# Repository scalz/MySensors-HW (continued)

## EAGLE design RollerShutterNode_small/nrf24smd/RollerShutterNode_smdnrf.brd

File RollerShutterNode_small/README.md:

# RollerShutterNode SMD version

It is a board for controlling rollershutter (0-100%) and detecting end stops.. Two relays for motor (UP and DOWN) and ACS712 for current sense of motor. 
You can connect 3 push buttons or an external i2c tactile device. This board can be used as dual relay board too, with current sense. It can control 12-220V motors.

Note : it is still in dev.

- Atmel328p TQFP
- NRF24 smd footprint
- ATSHA204A authentication footprint
- eeprom footprint for OTA
- ACS712 footprint
- 2x 5Amp relays : OMRON G6D-1A-ASI protected by TVS diode & small capacitor
- ac dc stepdown 220V-5V : HILINK_HLK-PM01 protected by varistor & ptc fuse
- 5mm pitch screw terminals
- I2C connector for optional tactile sensor chip
- 47mm x 48mm

Arduino Pin description :
- A0 : ADC ACS712
- A3 : ATSHA204A data
- D6 : Down Relay
- D7 : Up relay
- I2C connector : SDA, SCL, D3, D4

DC connectors : 
- SPI for programming Atmel328p
- FTDI for bootloading
- A1 : Up button
- A2 : Down button
- D5 : Stop button

AC Connector description :
- N : Neutral (Neutre)
- L : Live (Phase)
- 12_220 : optional. If using 220v motor, you need to tie it with Source on Motor Connector

Motor Connector description :
- Up : Up relay for motor
- Down : Down relay for motor
- Source : 12-24v motor source. If using 220v motor, tie it with 12_220 on AC Connector

In progress : 
- sketch for rollershutter (buttons, calibration functions, controlling 0-100%). 
- add Bill of Materials
- add gerbers for Seeed, Itead, and OSH fabhouses.

OPEN SOURCE

Copyright Scalz (2015). [Attribution-ShareAlike CC BY-SA](https://creativecommons.org/licenses/)

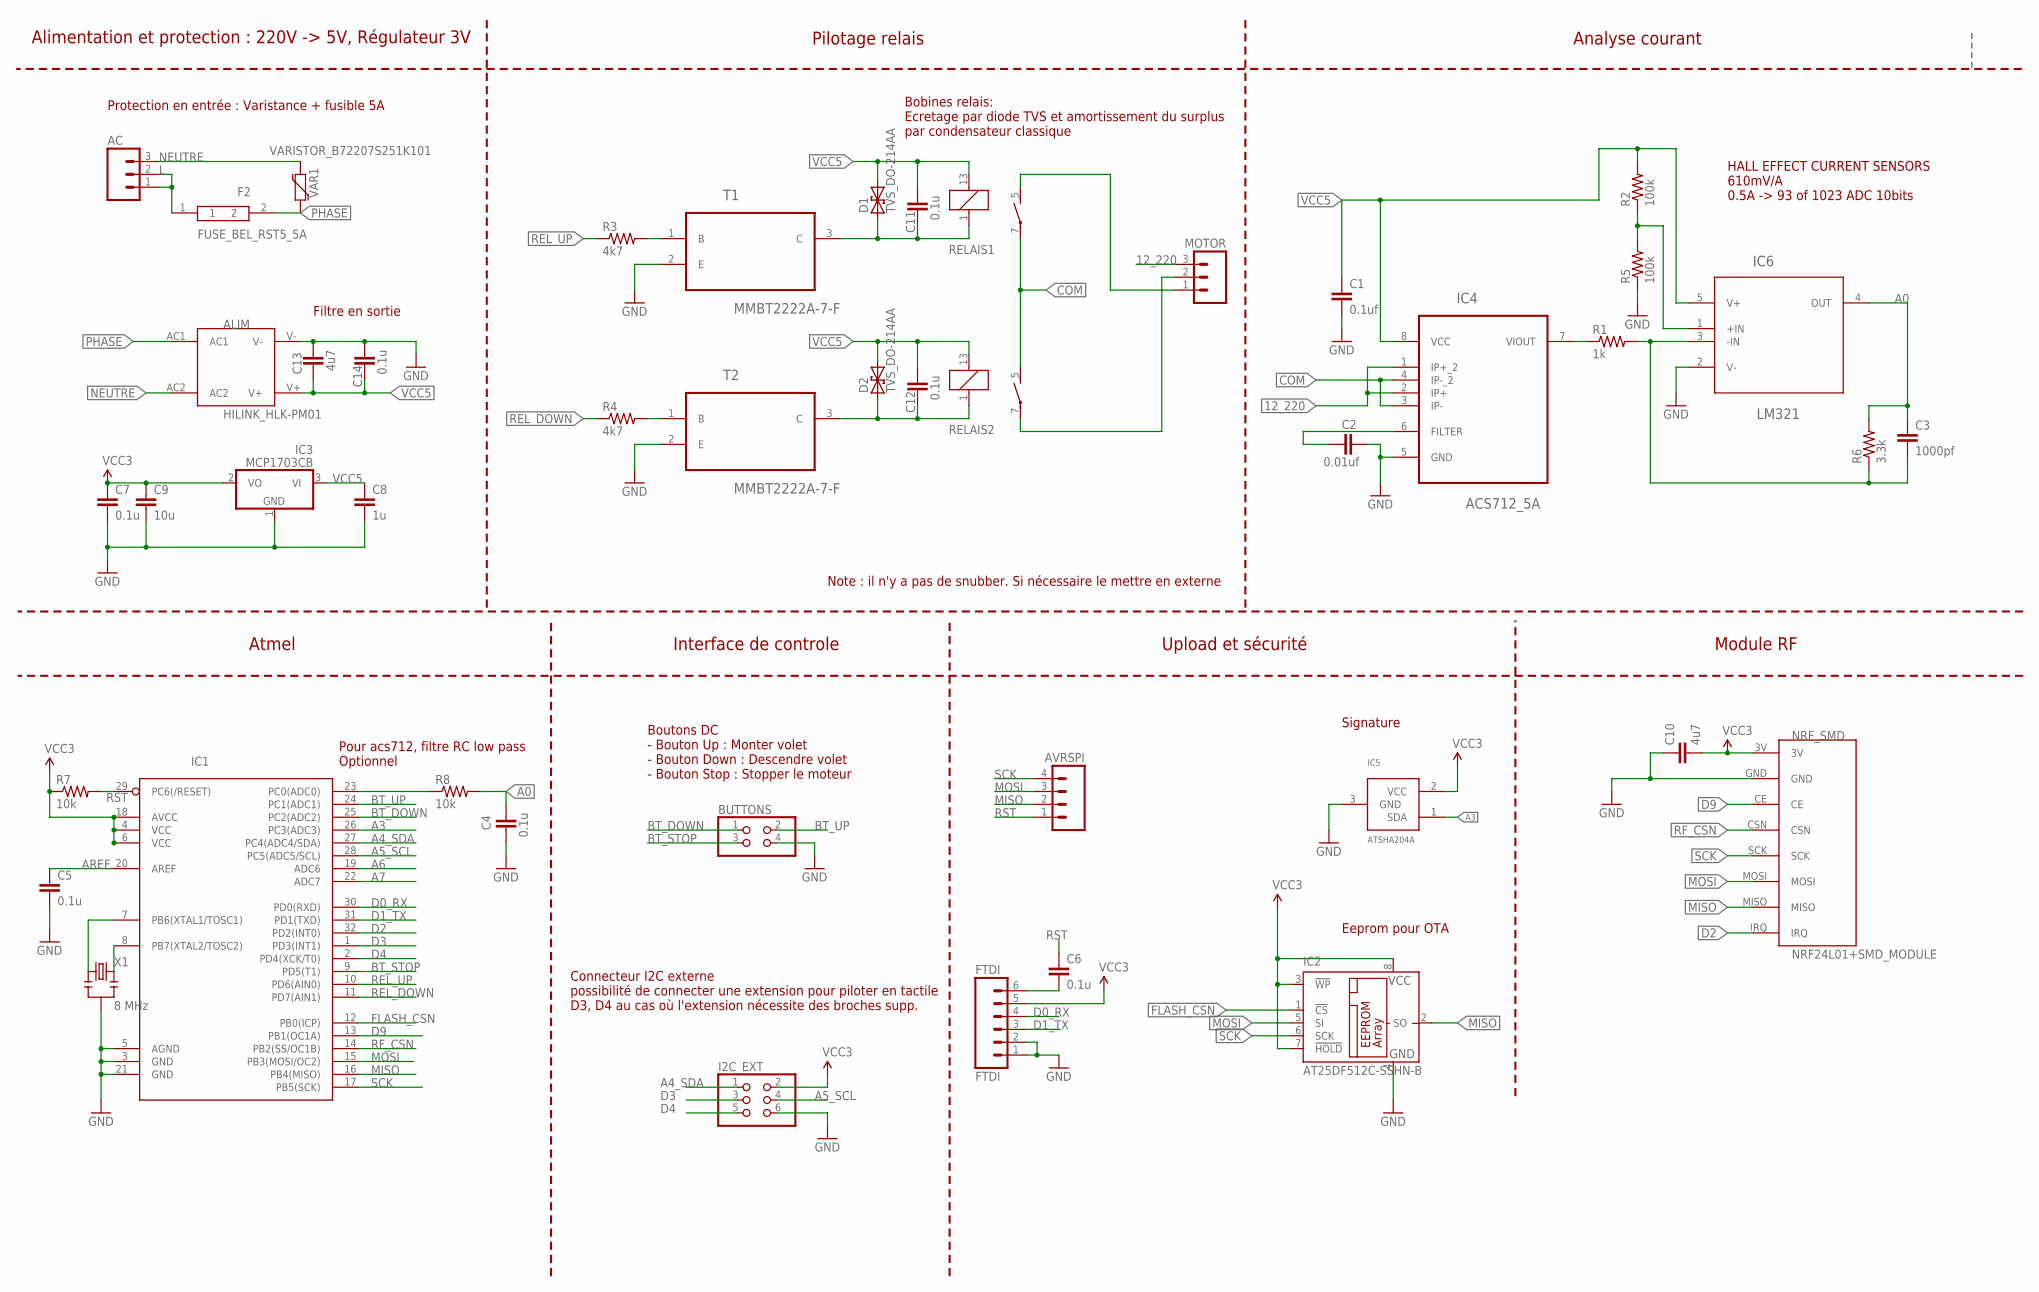
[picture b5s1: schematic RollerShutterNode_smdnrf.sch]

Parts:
AC: M03-SCREW-5MM; SCREWTERMINAL-5MM-3
ALIM: HILINK_HLK-PM01
AVRSPI: M04PTH; 1X04
BUTTONS: PINHD-2X2; 2X02
C1: 0.1uf; 0805-CAP
C2: 0.01uf; 0805-CAP
C3: 1000pf; 0805-CAP
C4, C5, C6, C7, C11, C12, C14: 0.1u; 0805-CAP
C8: 1u; 0805-CAP
C9: 10u; 0805-CAP
C10, C13: 4u7; 0805-CAP
D1, D2: TVS_DO-214AA
F2: FUSE_BEL_RST5_5A
FTDI: FTDI; 1X06
I2C_EXT: PINHD-2X3; 2X03
IC1: ATMega-328; TQFP32-08
IC2: AT25DF512C-SSHN-B; SO-08
IC3: MCP1703CB; SOT23
IC4: ACS712_5A; SOIC127P600X175-8N
IC5: ATSHA204A; SOT23
IC6: LM321; SOT95P285X120-5N
MOTOR: M03-SCREW-5MM; SCREWTERMINAL-5MM-3
NRF_SMD: NRF24L01+SMD_MODULE
R1: 1k; 0805-RES
R2, R5: 100k; 0805-RES
R3, R4: 4k7; 0805-RES
R6: 3.3k; 0805-RES
R7, R8: 10k; 0805-RES
RELAIS1, RELAIS2: Relais G6D; G6D
T1, T2: MMBT2222A-7-F; SOT103P240X110-3N
VAR1: VARISTOR_B72207S251K101
X1: 8 MHz; RESONATOR-SMD

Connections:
12_220: IC4.1 (IP+_2), IC4.2 (IP+), MOTOR.3
A0: C3.1, C4.2, IC6.4 (OUT), R6.2, R8.2
A3: IC1.26 (PC3(ADC3)), IC5.1 (SDA)
A4_SDA: I2C_EXT.1, IC1.27 (PC4(ADC4/SDA))
A5_SCL: I2C_EXT.4, IC1.28 (PC5(ADC5/SCL))
A6: IC1.19 (ADC6)
A7: IC1.22 (ADC7)
AREF: C5.1, IC1.20 (AREF)
BT_DOWN: BUTTONS.1, IC1.25 (PC2(ADC2))
BT_STOP: BUTTONS.3, IC1.9 (PD5(T1))
BT_UP: BUTTONS.2, IC1.24 (PC1(ADC1))
COM: IC4.3 (IP-), IC4.4 (IP-_2), RELAIS1.7, RELAIS2.5 (S)
D0_RX: FTDI.4, IC1.30 (PD0(RXD))
D1_TX: FTDI.3, IC1.31 (PD1(TXD))
D2: IC1.32 (PD2(INT0)), NRF_SMD.IRQ
D3: I2C_EXT.3, IC1.1 (PD3(INT1))
D4: I2C_EXT.5, IC1.2 (PD4(XCK/T0))
D9: IC1.13 (PB1(OC1A)), NRF_SMD.CE
FLASH_CSN: IC1.12 (PB0(ICP)), IC2.1 (!CS)
GND: ALIM.V-, BUTTONS.4, C1.2, C2.2, C4.1, C5.2, C7.2, C8.2, C9.2, C10.1, C13.2, C14.2, FTDI.1, FTDI.2, I2C_EXT.6, IC1.3 (GND), IC1.5 (AGND), IC1.21 (GND), IC2.4 (GND), IC3.1 (GND), IC4.5 (GND), IC5.3 (GND), IC6.2 (V-), NRF_SMD.GND, R5.1, T1.2 (E), T2.2 (E), X1.2
L: AC.1, AC.2, F2.1
MISO: AVRSPI.2, IC1.16 (PB4(MISO)), IC2.2 (SO), NRF_SMD.MISO
MOSI: AVRSPI.3, IC1.15 (PB3(MOSI/OC2)), IC2.5 (SI), NRF_SMD.MOSI
unnamed: C2.1, IC4.6 (FILTER)
unnamed: IC4.7 (VIOUT), R1.1
unnamed: R3.2, T1.1 (B)
unnamed: R4.2, T2.1 (B)
unnamed: C12.1, D2.A (1), RELAIS2.1, T2.3 (C)
unnamed: MOTOR.1, RELAIS1.5 (S)
unnamed: C11.1, D1.A (1), RELAIS1.1, T1.3 (C)
unnamed: MOTOR.2, RELAIS2.7
unnamed: C3.2, IC6.3 (-IN), R1.2, R6.1
unnamed: IC6.1 (+IN), R2.1, R5.2
unnamed: IC1.7 (PB6(XTAL1/TOSC1)), X1.1
unnamed: IC1.23 (PC0(ADC0)), R8.1
unnamed: C6.2, FTDI.6
unnamed: IC1.8 (PB7(XTAL2/TOSC2)), X1.3
NEUTRE: AC.3, ALIM.AC2, VAR1.1
PHASE: ALIM.AC1, F2.2, VAR1.2
REL_DOWN: IC1.11 (PD7(AIN1)), R4.1
REL_UP: IC1.10 (PD6(AIN0)), R3.1
RF_CSN: IC1.14 (PB2(SS/OC1B)), NRF_SMD.CSN
RST: AVRSPI.1, C6.1, IC1.29 (PC6(/RESET)), R7.2
SCK: AVRSPI.4, IC1.17 (PB5(SCK)), IC2.6 (SCK), NRF_SMD.SCK
VCC: C7.1, C9.1, C10.2, FTDI.5, I2C_EXT.2, IC1.4 (VCC), IC1.6 (VCC), IC1.18 (AVCC), IC2.3 (!WP), IC2.7 (!HOLD), IC2.8 (VCC), IC3.2 (VO), IC5.2 (VCC), NRF_SMD.3V, R7.1
VCC5: ALIM.V+, C1.1, C8.1, C11.2, C12.2, C13.1, C14.1, D1.C (2), D2.C (2), IC3.3 (VI), IC4.8 (VCC), IC6.5 (V+), R2.2, RELAIS1.13 (2), RELAIS2.13 (2)

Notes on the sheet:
HALL EFFECT CURRENT SENSORS 610mV/A 0.5A -> 93 of 1023 ADC 10bits
Eeprom pour OTA
Signature
Interface de controle
Boutons DC - Bouton Up : Monter volet - Bouton Down : Descendre volet - Bouton Stop : Stopper le moteur
Connecteur I2C externe possibilité de connecter une extension pour piloter en tactile D3, D4 au cas où l'extension nécessite des broches supp.
Protection en entrée : Varistance + fusible 5A
Bobines relais: Ecretage par diode TVS et amortissement du surplus par condensateur classique
Alimentation et protection : 220V -> 5V, Régulateur 3V
Pilotage relais
Analyse courant
Upload et sécurité
Module RF
Atmel
Pour acs712, filtre RC low pass Optionnel
Filtre en sortie
Note : il n'y a pas de snubber. Si nécessaire le mettre en externe

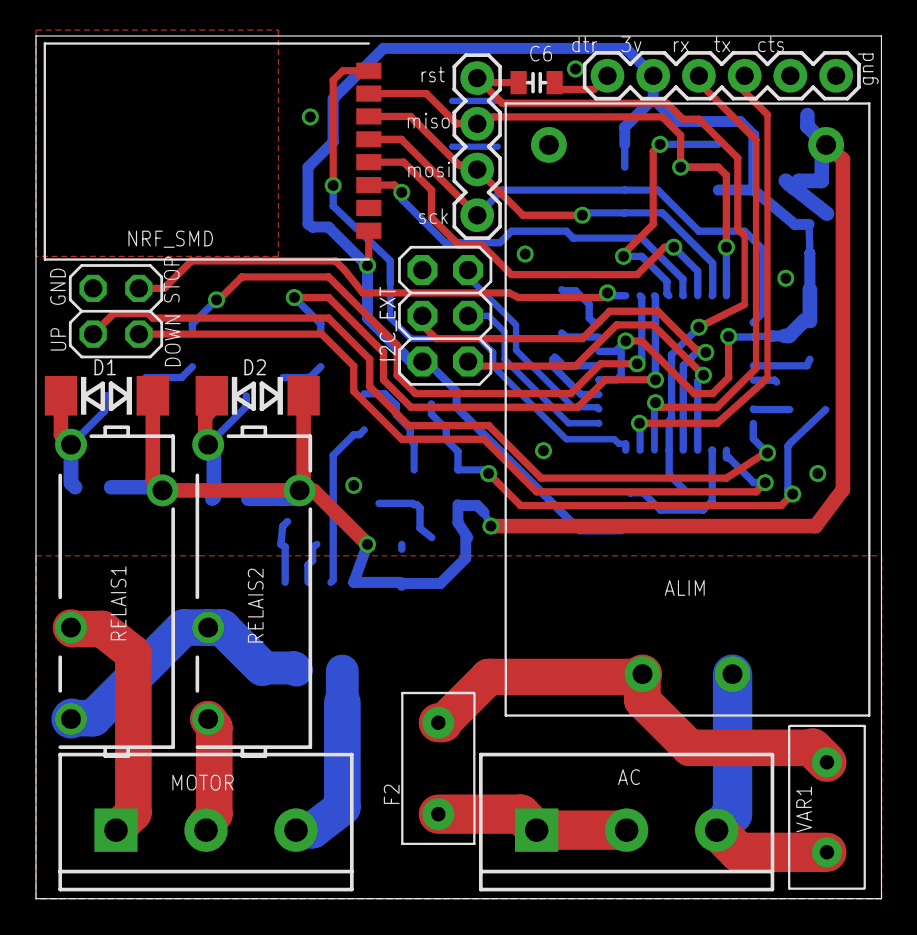
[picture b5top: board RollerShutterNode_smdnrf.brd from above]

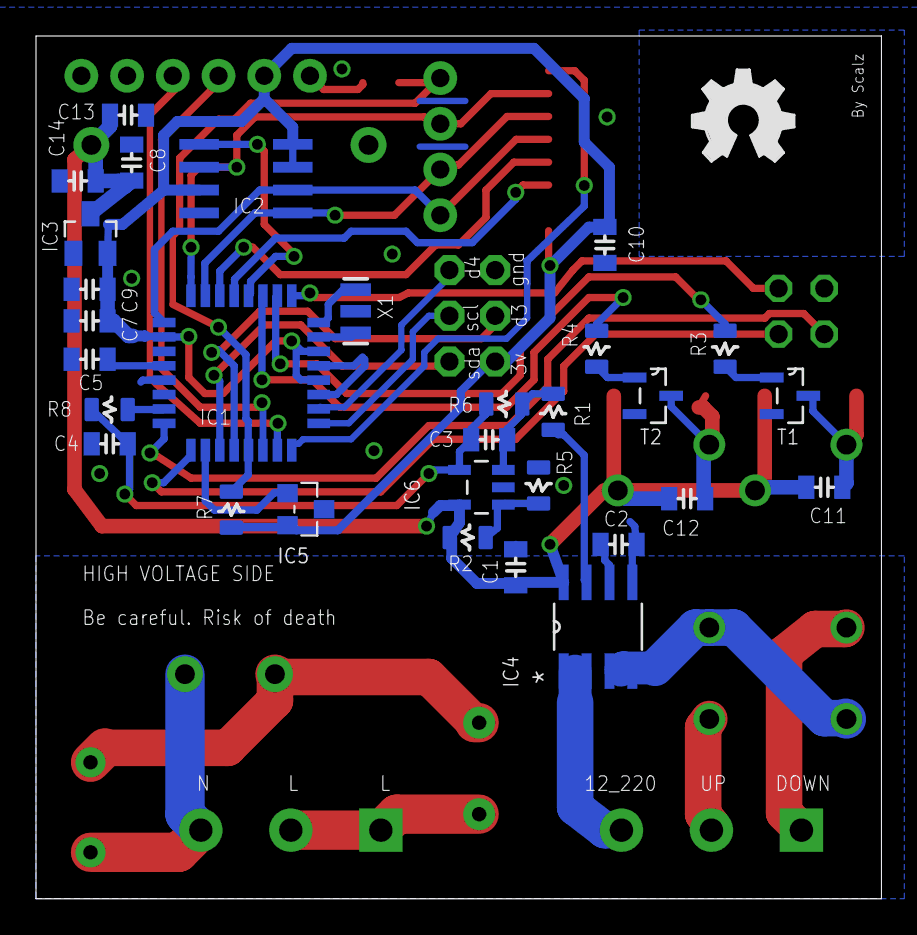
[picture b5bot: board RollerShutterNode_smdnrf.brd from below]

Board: 2 copper layers, 47.0 x 47.9 mm, 46 parts (31 on the bottom side), 44 nets.

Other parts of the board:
U$4: OSHW_FILLX200_NOTEXT

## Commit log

2015-06-10 :octocat: Added .gitattributes & .gitignore files
2015-06-10 OneRelayMySensors upload
2015-06-10 Upload boards and desc
2015-06-10 License update
2015-06-10 upload schem
2015-06-10 Nrf24 smd module footprint added in file 2.sch
2015-06-11 jst connector added
2015-06-13 changes
    -res + zener to flash mem avoid fry
    - dual schottky instead two single
    - minor component ref changes
2015-06-13 rst pin on arduino pro mini connected
2015-06-13 change
2015-06-13 silkscreen changed, Bom added
2015-06-13 add gerber
2015-06-15 Mysensors GW esp8266 project added
2015-06-24 relay footprint, changes res size
2015-06-26 RollerShutterNode
    My workspace : RollershutterNode for Mysensors.
2015-06-26 add schem pdf
2015-06-28 fuse removed, added 12-220v motor control
    Need to use external fuse and snubber if needed
2015-06-28 desc change
2015-07-01 gnd plane under nrf removed
2015-07-01 Roller shutter node for MySensors (nrf smd only)
2015-07-01 readme update
2015-07-01 render temp
2015-07-02 render temp test
2015-07-02 gnd plane modified for nrf24
2015-07-05 Mosfet + Pull up on LM8364 reset
    Pull up on lm8364 was missing. oops. So mosfet and pull up added to
    invert signal. Schem changed. Little change for radios gnd plane. BOM
    changed
2015-07-05 Board config overview
    Jumpers and connectors description
2015-07-05 overview
2015-07-12 remove temporarly dc booster board
2015-07-12 change on mosfet power (error in previous version)
2015-07-18 overview update
2015-07-21 temparily remove brd files, some changes needed
2015-07-28 Changes in progress, ncp302 added in place of lm834
    some files deleted, will be back soon,
2015-07-28 routing minor changes
2015-07-29 many changes
    removed external TX and RX
    External I2C3 added
    Reverse polarity added
    Optional pull up for D6 added
2015-07-29 temporily remove
2015-07-30 Optional pullups Added, description..
2015-07-30 readme change
2015-07-30 minor change
2015-07-31 rerouting eeprom for ota
2015-08-04 remove temporily for routing
2015-08-07 rev1 update
2015-08-07 fuse ref updated
2015-08-07 fuse ref changed
2015-08-07 reup
2015-08-08 adc rc low pass filter added, temp bom added
2015-08-11 rev1 update
    rev1: it's time to send it to fabhouse!
2015-08-11 some cleanings in progress..
2015-08-16 temp img upload
2015-08-22 MyTinyCamel
    init project
2015-08-22 temp schematics added
2015-08-22 img up
2015-08-23 overview and license
2015-08-23 decoupl capa for 5vdc booster, pull up, down for d3
2015-08-25 mcp1640 ref update -> mcp1640t-ichy PWM/PFM
2015-08-30 JP9 jumper added
2015-08-30 screenshots and bom added
2015-08-30 readme
2015-08-30 gerbers rev1
2015-08-30 eagle files
2015-08-30 remove
2015-08-31 overview update, hole size update
2015-08-31 temp problem with update non updated!!strange so reupload of overview..
2015-08-31 overview reup
2015-08-31 upd problem, remove and reup...
2015-08-31 img folder reup because it doesn't want to refresh...
2015-09-09 MyMultiSensorChild rep created
2015-09-20 remove gerbers
    will be replaced by rev1.1
2015-11-05 clean repo
    refactory
2015-11-05 RollerShutterNode
2015-11-05 img update
2015-11-15 Low power PIR breakout board
2015-11-15 clean
2015-11-15 rfm69 version added
2015-11-16 check
2015-11-16 1.1 update
    there was a missing mistake I didn't see even if I checked lot of
    times...routing derouting mistake...spst relay was always ON. shame on
    me!
2015-12-11 temp bom added
2016-01-21 silkscreen updated, bom added
2016-03-27 some rerouting and a small fix on connector
2016-04-15 temporary removed
2016-04-15 Mymultisensorcoincell project added
2016-04-18 silk change
2016-08-12 release preparation: readme update
2016-08-12 release preparation : readme update
2016-08-12 release preparation: still readme update
2016-08-12 release preparation : readme update again..damn!
2016-08-12 removed
2016-08-12 temp
2016-08-12 still readme
2016-08-12 release 1.3 for rfm69 version
2016-08-13 revision 1.3 release : nrf24smd version
2016-10-16 Rollershutter node sketch v1.0
2016-10-20 nrf24 minor fix
    CSN was not connected in pcb! whereas it was in schematics..
2016-12-04 clean repo
2018-02-23 Fixed Markdown Style
2020-02-25 Update MyNodeDefinition.h
    added MY_TRANSPORT_WAIT_READY_MS to make the node start even if no gateway is available
    changed FORCE_TRANSMIT_INTERVAL to milliseconds
2020-02-25 Update MyRollershutter.ino
    Add forced transmission after FORCE_TRANSMISSION_INTERVAL
